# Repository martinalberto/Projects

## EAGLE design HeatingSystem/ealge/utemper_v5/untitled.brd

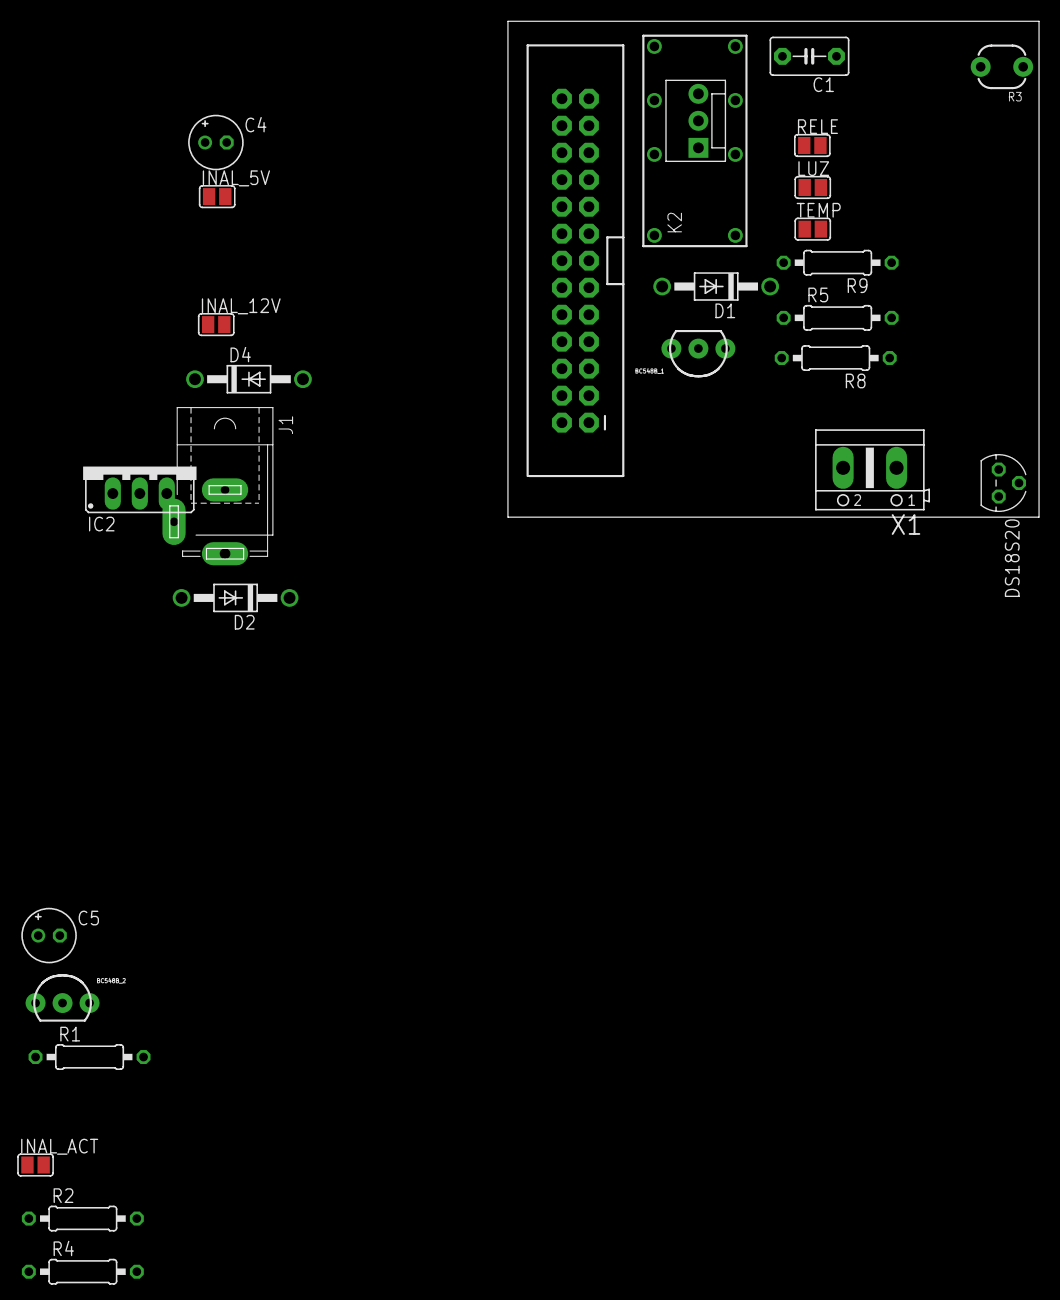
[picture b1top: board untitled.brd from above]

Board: 2 copper layers, 29 parts (0 on the bottom side), 21 nets, no tracks yet.

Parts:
BC548B_1, BC548B_2: TO-92-AMMO
C1: 1uF; C5B3.5
C4, C5: 10uF; E2-5
D1, D2, D4: 1N4004; DO41-10
DS18S20: TO-92
IC2: 78XXS
INAL_5V, INAL_12V: SJ
INAL_ACT: SJ
J1: SPC4077
JP1: MOLEX-1X3
JP2: RASPBERRYPI-GPIOPTH; 2X13-SHROUDED
K2: DS2Y-S-DC5V; DS2Y
LUZ: SJ
R1, R2, R8: 1K; 0207/10
R3: PHOTOCELLPTH-KIT; PHOTOCELL-KIT
R4: 10K; 0207/10
R5: 2.2K; 0207/10
R9: 4.7K; 0207/10
RELE: SJ
TEMP: SJ
U$1: OSHW-LOGOL; OSHW-LOGO-L
X1: AK500/2

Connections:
+3V3: JP2.1, LUZ.2, R4.1, TEMP.2
+5V: C5.+, D2.C, IC2.OUT, INAL_5V.1, JP2.2, RELE.2
+12V: C4.+, D4.C, IC2.IN, INAL_12V.1, J1.3
GND12: BC548B_1.1, C1.2, C4.-, C5.-, D2.A, D4.A, DS18S20.3, IC2.GND, J1.2, JP1.1, JP2.6, JP2.9, JP2.14, JP2.20, JP2.25, K2.13
GPIO1: JP2.5, R8.2
GPIO4: DS18S20.2, JP2.7, R9.2
GPIO14: INAL_ACT.1, JP2.8, R1.2
GPIO23: C1.1, JP2.16, R3.1
unnamed: BC548B_1.3, D1.A, K2.16
unnamed: DS18S20.1, R9.1, TEMP.1
unnamed: R3.2, R5.1
unnamed: BC548B_1.2, R8.1
unnamed: BC548B_2.2, R1.1
unnamed: K2.8, X1.2
unnamed: BC548B_2.1, INAL_ACT.2, JP1.2
unnamed: K2.11, R2.1
unnamed: K2.4, X1.1
unnamed: LUZ.1, R5.2
unnamed: D1.C, K2.1, RELE.1
unnamed: R2.2, R4.2
unnamed: BC548B_2.3, INAL_5V.2, INAL_12V.2, JP1.3

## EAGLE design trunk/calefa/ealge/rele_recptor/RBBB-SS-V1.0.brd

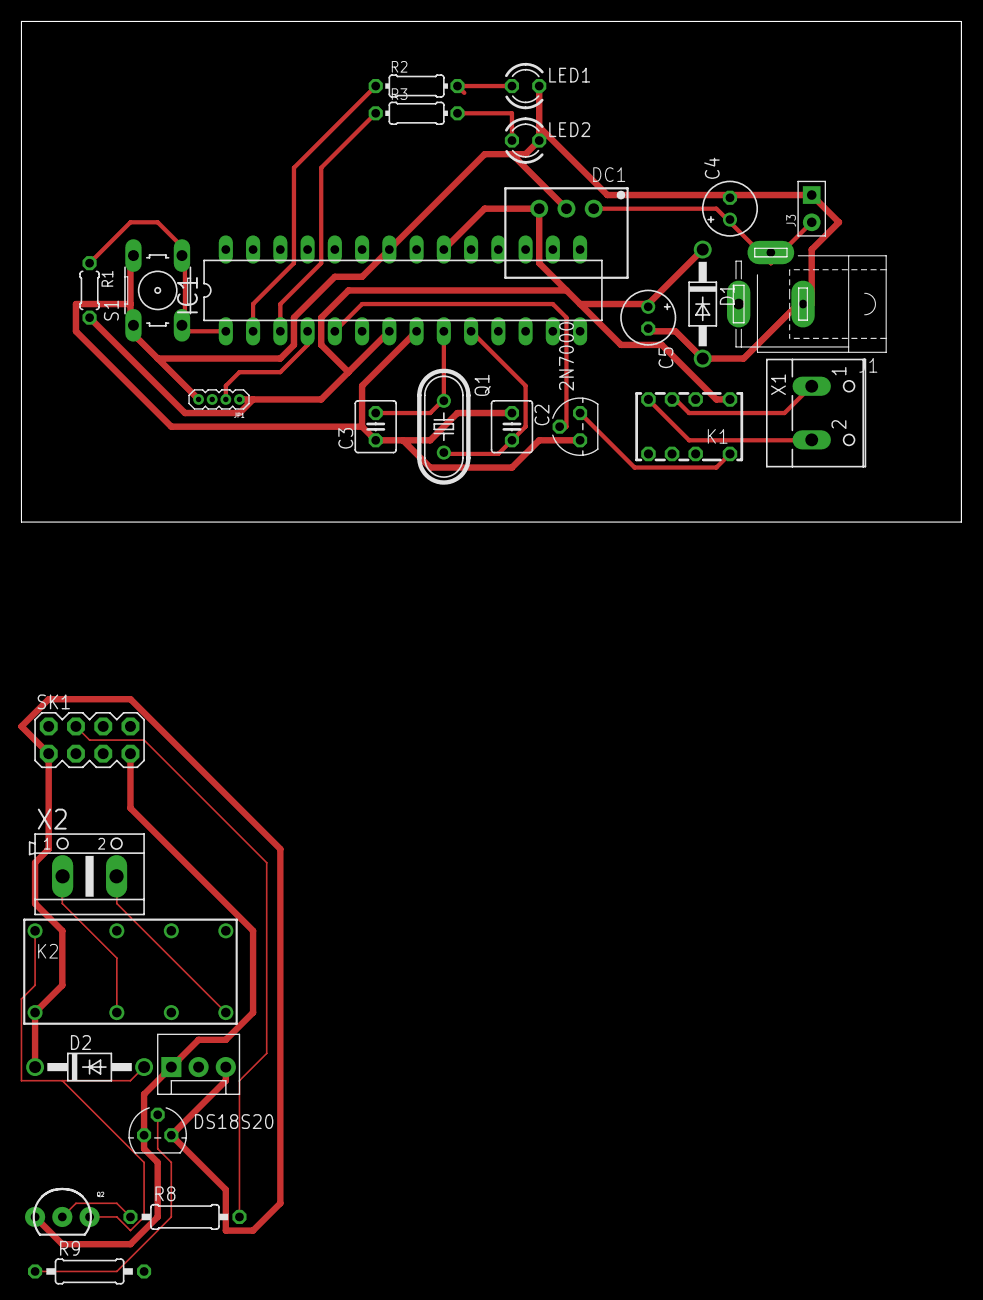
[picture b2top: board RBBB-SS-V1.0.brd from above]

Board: 2 copper layers, 87.6 x 46.7 mm, 29 parts (0 on the bottom side), 24 nets.

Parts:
2N7000: TN0602N3; TO-92
C2, C3: 22pF; C025-040X050
C4, C5: 10uF; E2-5
D1, D2: 1N4004; DO41-10
DC1: R-78C1.8-1.0; SIP3
DS18S20: TO-92
IC1: ATmega168; DIL28-3
J1: SPC4077
J3: 2P-2.54-65/35MIL
JP1: 1X04-1.27MM
JP2: MOLEX-1X3
K1: G6K-2P-Y
K2: DS2Y-S-DC5V; DS2Y
LED1: TLLG4400; LED3MM
LED2: TLLR4400; LED3MM
Q1: 16Mhz; HC49U-V
Q2: TO-92-AMMO
R1: 10k; 0204/5
R2, R3: 0204/7
R8: 1K; 0207/10
R9: 4.7K; 0207/10
S1: B3F-10XX
SK1: PI-AUX-AUX-PTH; GPIO-AUX-CONNECTOR
X1: W237-102
X2: AK500/2

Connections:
+5V: C5.+, D1.C, D2.C, DC1.3, DS18S20.1, IC1.7, IC1.20, JP1.1, JP2.3, K1.1, K2.1, R1.2, SK1.1
DGND: DS18S20.3, JP2.1, Q2.1, SK1.7
GND: 2N7000.1, C2.1, C3.1, C4.-, C5.-, D1.A, DC1.2, IC1.8, IC1.22, J1.1, J3.1, JP1.4, LED1.K, LED2.K, S1.1, S1.2, SK1.8
GPIO0: R8.2, SK1.4
GPIO8: JP2.2, SK1.3
GPIO14: R9.2, SK1.6
unnamed: C4.+, DC1.1, J1.2, J3.2
unnamed: IC1.2, R2.1
unnamed: LED1.A, R2.2
unnamed: IC1.3, R3.1
unnamed: LED2.A, R3.2
unnamed: C3.2, IC1.9, Q1.1
unnamed: C2.2, IC1.10, Q1.2
unnamed: 2N7000.3, K1.8
unnamed: Q2.2, R8.1
unnamed: DS18S20.2, R9.1
unnamed: K1.4, X1.2
unnamed: K1.3, X1.1
unnamed: 2N7000.2, IC1.5
unnamed: IC1.4, JP1.2
unnamed: D2.A, K2.16, Q2.3
unnamed: K2.8, X2.2
unnamed: K2.4, X2.1
RESET: IC1.1, R1.1, S1.3, S1.4

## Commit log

2013-11-30 Initial directory structure.
2013-12-17 calefacon.py start
2013-12-17 calefacon_sh start.
2013-12-18 Created wiki page through web user interface.
2013-12-18 i empezamos con los script de calefa.
2013-12-18 Deleted wiki page calefacon_sh through web user interface.
2013-12-18 bot que actuliza la portada de la wikiquote
2013-12-18 mitter
2013-12-19 actulizacion.
2013-12-20 i le incluimos sistemas de log por fichero
2013-12-22 conetart por wifi.
2014-01-02 Include lib of bcm2835
2014-01-10 new proyect: Ardruino control led RGB.
2014-01-10 i Update to last version of progrtam.
2014-02-11 Edited wiki page calefacon_py through web user interface. include code label.
2014-02-11 Created wiki page through web user interface. http://learn.adafruit.com/pi-thermal-printer/pi-setup-part-2
2014-03-25 SCREEN_2.4
2014-03-25 equipo remoto.
2014-04-25 actualizacion
2014-05-12 primer conmit
2014-05-12 depurados estados, ahora siempre envía datos.
2014-05-15 nueva version
2014-05-16 fix errors.
2014-05-21 utemper actulizado y libreria wifi.
2014-05-21 fix errores
2014-05-22 incluimos wifi y la temperatura dentro del utemper.py
2014-05-22 ya no se usa es conectar wifi
2014-06-21 incluir la primera versión de web movil.
2014-07-01 Nuevo estado,
2014-09-03 Nuevos cambios
2014-09-04 new boton 1
2014-09-30 nuevas imagenes
2014-09-30 ficheros
2014-10-10 menos time
2014-10-10 improve some thing
2014-10-12 last cambios
2014-10-13 boton apagado
2014-10-13 more icon
2014-10-13 screen modo calefa
2014-10-14 remove personal information.
2014-10-27 last version
2014-11-03 last update.
2014-11-26 prueba1
2014-12-12 version +1
2015-04-27 fix error.
2015-08-27 Migrating wiki contents from Google Code
2015-08-27 Create Portal Cautivo.txt
    Translado desde Google Code Wiki,
2015-10-18 Calefcon old version.
2015-10-18 order calefcon
    order calefcon
2015-10-18 fix errors.
    fix errors.
2015-10-18 fix error
    fix error and xively with config.
2015-11-05 New images.
2015-11-05 new Class Report grovestreams.
2015-11-07 Include secction web
2015-11-07 folder Raspberry pi. Python thermal Printer
2015-11-07 Fix errors. reports and in casa.
2015-11-09 fix littel errors.
2015-11-11 PiTFT board
2015-11-11 squematic board.
2015-12-13 Web Internal
2015-12-13 Folder Caja.
2015-12-13 update Ardruino Folder.
2015-12-13 sensor 433
2016-12-22 Cambiamos Nombre de la carpeta Principal para el sistema.
2016-12-22 RetroPieBox. Original Files.
2016-12-22 first version.
2016-12-22 All files.
2016-12-22 Include Images.
2017-01-12 Esquema Conexion modulos.
2017-07-12 Decode data from Traker TK103 binary GT06.
2017-08-11 Poyecto:Check Agua.
2017-10-25 Update Version: Possible fail, if traker don't send position message.
2017-10-25 New Proyect: Printer Cam
2017-10-25 New Proyect: Check if yesterday rain by mobile
2017-11-07 Update to last version.
2017-11-14 new Version, Mode Economy.
2017-11-14 Remove PrintercCam.WakeUp
2017-12-16 Update module weather.
2017-12-16 Remove Reports and inclune new images.
2017-12-16 new Images
2018-05-09 Update Proyect LED_RGB. Version 2: Ambilight for TV.
2018-05-09 Update Script to Telegram, (Yowsup -> Telegram Client python).
2018-05-09 Thermal-Printer inside the Printer Cam.
2019-02-15 Printer Cam: Update: Last stable version.
    Include all file necesary.
    Folder for Imange files.
2019-02-15 Minor Change
2019-02-15 Minor Change: Restart Files, Rename code folder.
2019-02-20 UTEMPER: Update Read Temperature by UDP Socket.
2019-02-21 Utemper: fix bug.

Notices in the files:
parts and their libraries:
SparkFun-Boards: Licensing: Creative Commons ShareAlike 4.0 International - https://creativecommons.org/licenses/by-sa/4.0
SparkFun: Licensing: CC v3.0 Share-Alike You are welcome to use this library for commercial purposes.
